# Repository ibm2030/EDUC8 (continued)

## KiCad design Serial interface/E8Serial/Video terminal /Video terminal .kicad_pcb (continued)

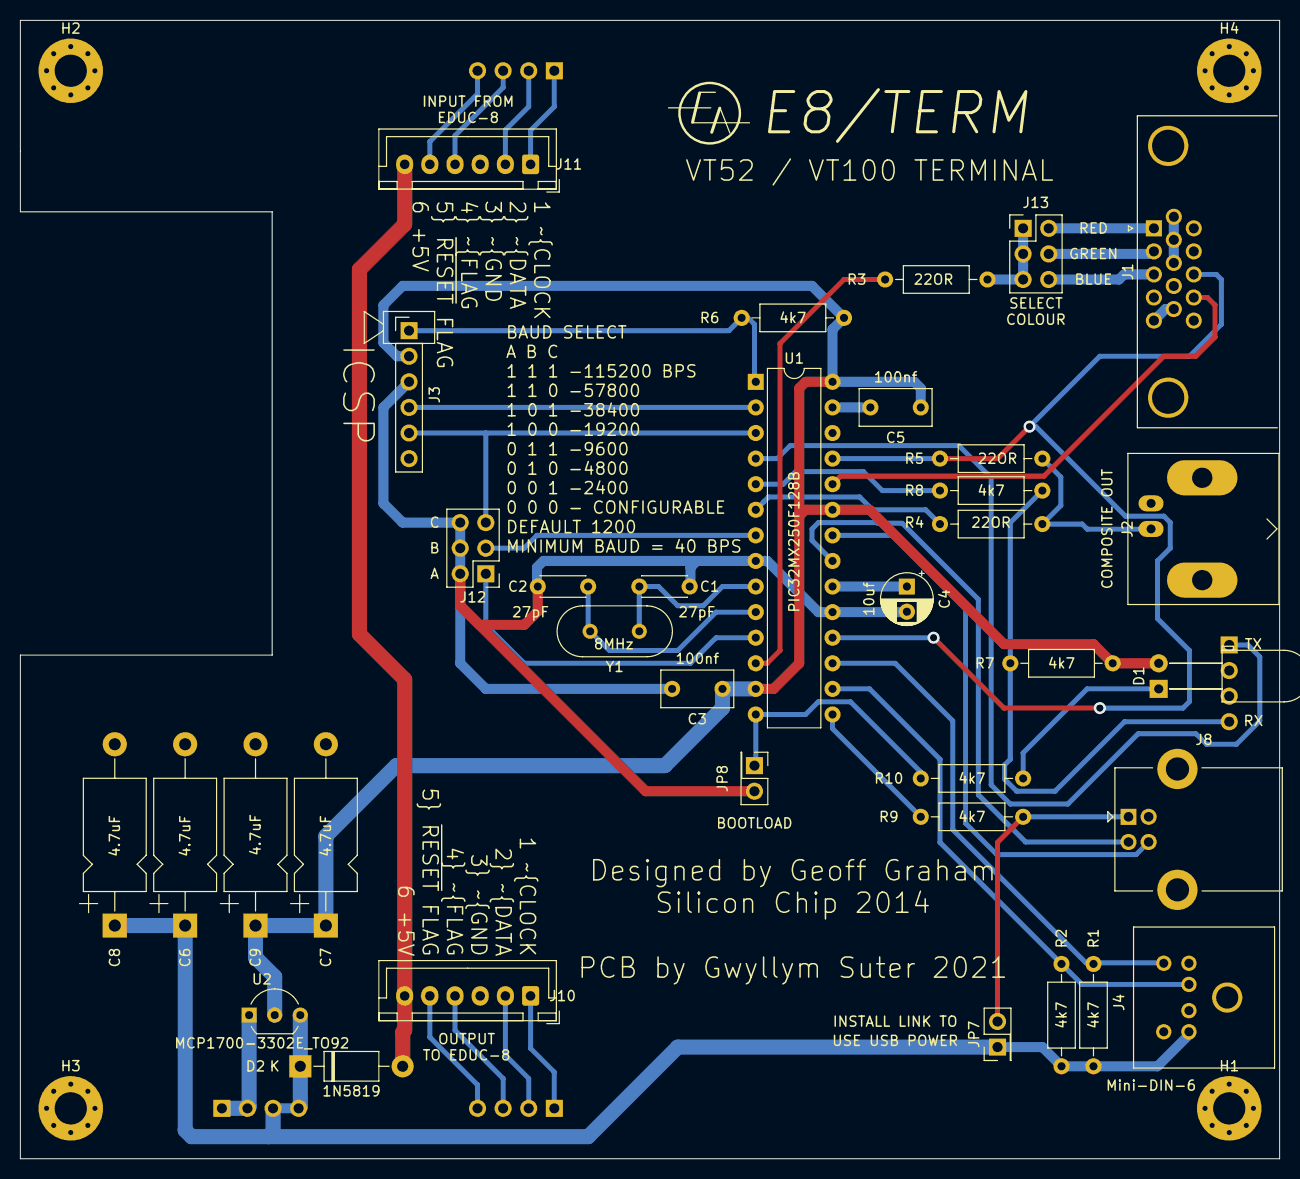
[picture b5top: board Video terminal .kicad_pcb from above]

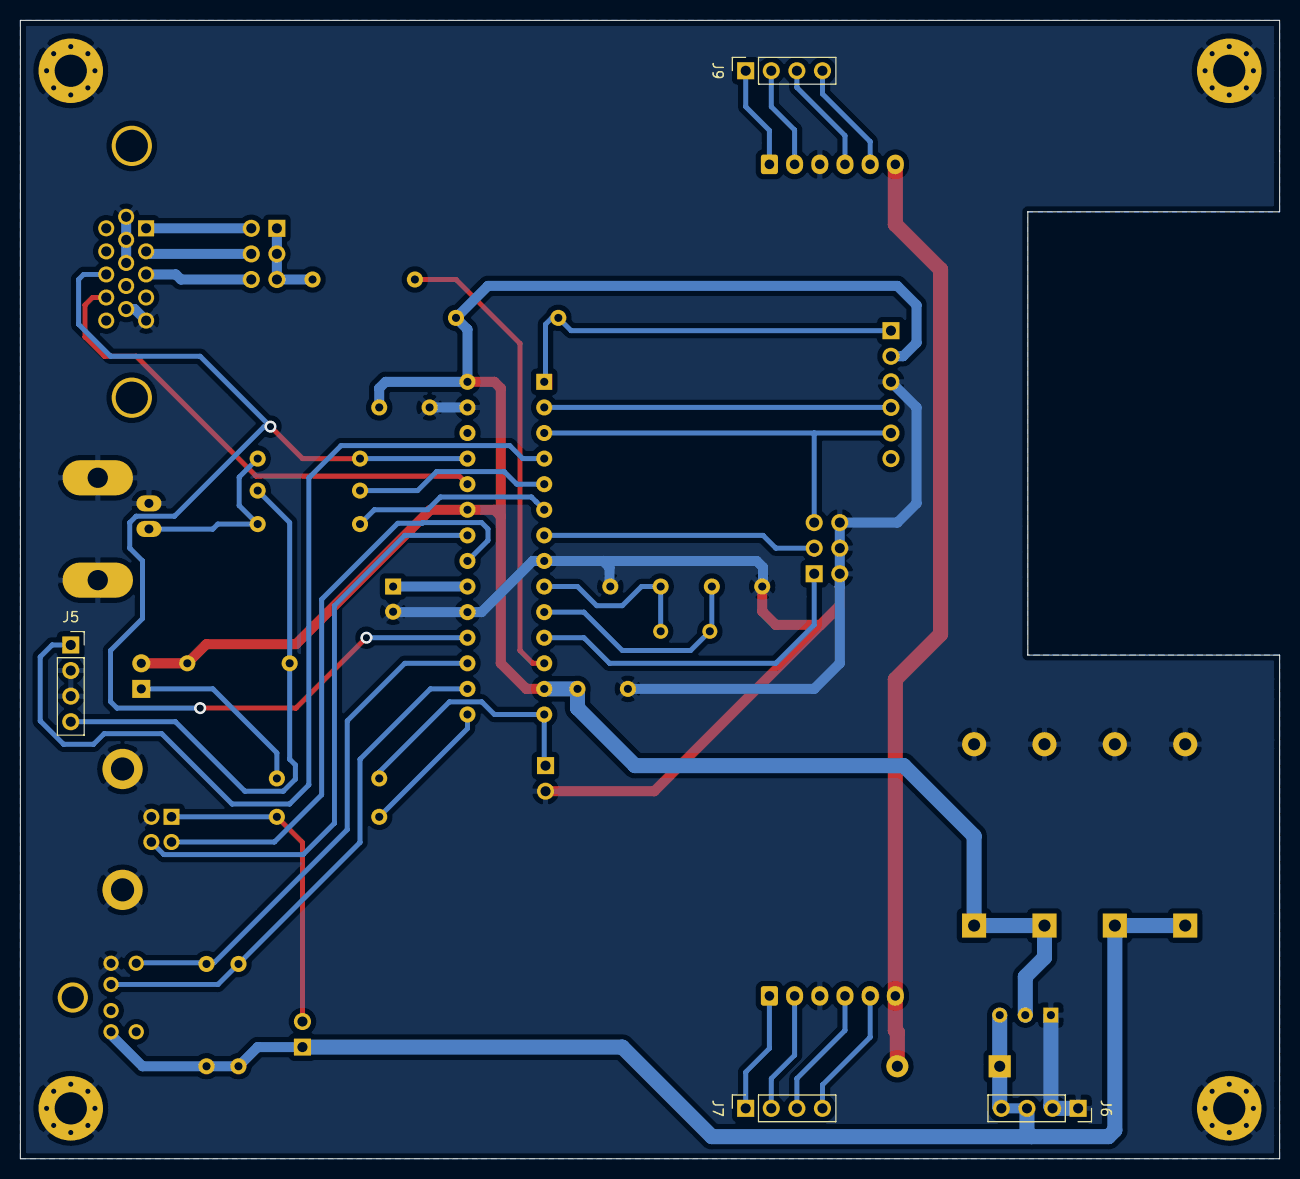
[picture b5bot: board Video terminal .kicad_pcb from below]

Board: 2 copper layers, 125.0 x 113.0 mm, 43 parts (4 on the bottom side), 40 nets.

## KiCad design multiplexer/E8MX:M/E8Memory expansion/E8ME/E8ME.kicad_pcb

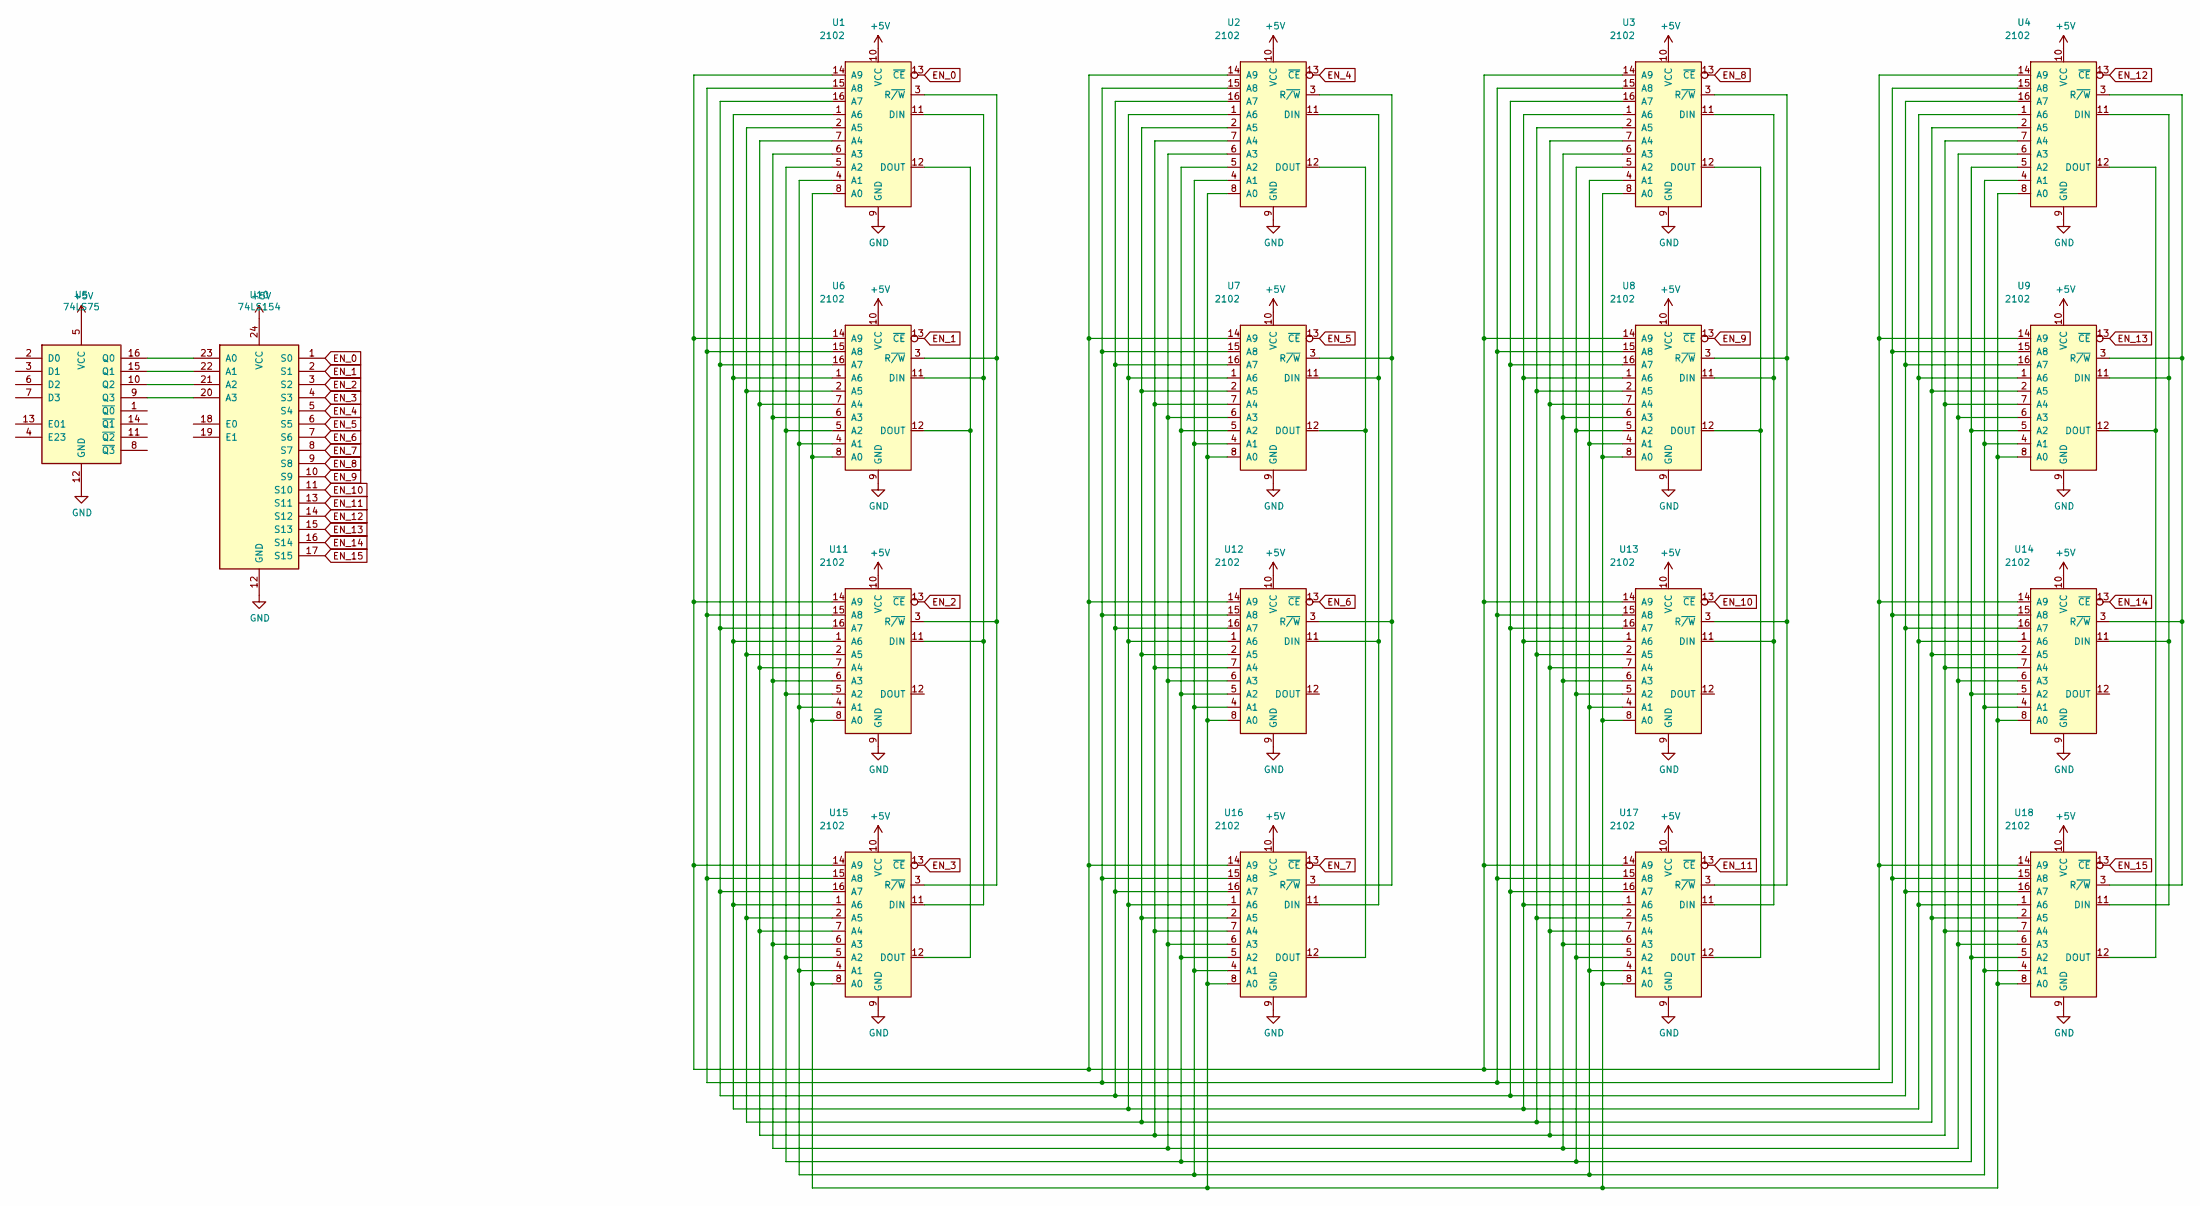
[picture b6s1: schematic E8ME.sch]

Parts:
U1, U2, U3, U4, U6, U7, U8, U9, U11, U12, U13, U14, U15, U16, U17, U18: 2102; DIP-16_W7.62mm_LongPads
U5: 74LS75; DIP-16_W7.62mm_LongPads
U10: 74LS154; DIP-24_W15.24mm_LongPads

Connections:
+5V: U1.10 (VCC), U2.10 (VCC), U3.10 (VCC), U4.10 (VCC), U5.5 (VCC), U6.10 (VCC), U7.10 (VCC), U8.10 (VCC), U9.10 (VCC), U10.24 (VCC), U11.10 (VCC), U12.10 (VCC), U13.10 (VCC), U14.10 (VCC), U15.10 (VCC), U16.10 (VCC), U17.10 (VCC), U18.10 (VCC)
EN_0: U1.13 (~CE), U10.1 (S0)
EN_1: U6.13 (~CE), U10.2 (S1)
EN_2: U10.3 (S2), U11.13 (~CE)
EN_3: U10.4 (S3), U15.13 (~CE)
EN_4: U2.13 (~CE), U10.5 (S4)
EN_5: U7.13 (~CE), U10.6 (S5)
EN_6: U10.7 (S6), U12.13 (~CE)
EN_7: U10.8 (S7), U16.13 (~CE)
EN_8: U3.13 (~CE), U10.9 (S8)
EN_9: U8.13 (~CE), U10.10 (S9)
EN_10: U10.11 (S10), U13.13 (~CE)
EN_11: U10.13 (S11), U17.13 (~CE)
EN_12: U4.13 (~CE), U10.14 (S12)
EN_13: U9.13 (~CE), U10.15 (S13)
EN_14: U10.16 (S14), U14.13 (~CE)
EN_15: U10.17 (S15), U18.13 (~CE)
GND: U1.9 (GND), U2.9 (GND), U3.9 (GND), U4.9 (GND), U5.12 (GND), U6.9 (GND), U7.9 (GND), U8.9 (GND), U9.9 (GND), U10.12 (GND), U11.9 (GND), U12.9 (GND), U13.9 (GND), U14.9 (GND), U15.9 (GND), U16.9 (GND), U17.9 (GND), U18.9 (GND)
unnamed: U1.1 (A6), U2.1 (A6), U3.1 (A6), U4.1 (A6), U6.1 (A6), U7.1 (A6), U8.1 (A6), U9.1 (A6), U11.1 (A6), U12.1 (A6), U13.1 (A6), U14.1 (A6), U15.1 (A6), U16.1 (A6), U17.1 (A6), U18.1 (A6)
unnamed: U1.2 (A5), U2.2 (A5), U3.2 (A5), U4.2 (A5), U6.2 (A5), U7.2 (A5), U8.2 (A5), U9.2 (A5), U11.2 (A5), U12.2 (A5), U13.2 (A5), U14.2 (A5), U15.2 (A5), U16.2 (A5), U17.2 (A5), U18.2 (A5)
unnamed: U1.3 (R~/W), U6.3 (R~/W), U11.3 (R~/W), U15.3 (R~/W)
unnamed: U1.4 (A1), U2.4 (A1), U3.4 (A1), U4.4 (A1), U6.4 (A1), U7.4 (A1), U8.4 (A1), U9.4 (A1), U11.4 (A1), U12.4 (A1), U13.4 (A1), U14.4 (A1), U15.4 (A1), U16.4 (A1), U17.4 (A1), U18.4 (A1)
unnamed: U1.5 (A2), U2.5 (A2), U3.5 (A2), U4.5 (A2), U6.5 (A2), U7.5 (A2), U8.5 (A2), U9.5 (A2), U11.5 (A2), U12.5 (A2), U13.5 (A2), U14.5 (A2), U15.5 (A2), U16.5 (A2), U17.5 (A2), U18.5 (A2)
unnamed: U1.6 (A3), U2.6 (A3), U3.6 (A3), U4.6 (A3), U6.6 (A3), U7.6 (A3), U8.6 (A3), U9.6 (A3), U11.6 (A3), U12.6 (A3), U13.6 (A3), U14.6 (A3), U15.6 (A3), U16.6 (A3), U17.6 (A3), U18.6 (A3)
unnamed: U1.7 (A4), U2.7 (A4), U3.7 (A4), U4.7 (A4), U6.7 (A4), U7.7 (A4), U8.7 (A4), U9.7 (A4), U11.7 (A4), U12.7 (A4), U13.7 (A4), U14.7 (A4), U15.7 (A4), U16.7 (A4), U17.7 (A4), U18.7 (A4)
unnamed: U1.8 (A0), U2.8 (A0), U3.8 (A0), U4.8 (A0), U6.8 (A0), U7.8 (A0), U8.8 (A0), U9.8 (A0), U11.8 (A0), U12.8 (A0), U13.8 (A0), U14.8 (A0), U15.8 (A0), U16.8 (A0), U17.8 (A0), U18.8 (A0)
unnamed: U1.11 (DIN), U6.11 (DIN), U11.11 (DIN), U15.11 (DIN)
unnamed: U1.12 (DOUT), U6.12 (DOUT), U15.12 (DOUT)
unnamed: U1.14 (A9), U2.14 (A9), U3.14 (A9), U4.14 (A9), U6.14 (A9), U7.14 (A9), U8.14 (A9), U9.14 (A9), U11.14 (A9), U12.14 (A9), U13.14 (A9), U14.14 (A9), U15.14 (A9), U16.14 (A9), U17.14 (A9), U18.14 (A9)
unnamed: U1.15 (A8), U2.15 (A8), U3.15 (A8), U4.15 (A8), U6.15 (A8), U7.15 (A8), U8.15 (A8), U9.15 (A8), U11.15 (A8), U12.15 (A8), U13.15 (A8), U14.15 (A8), U15.15 (A8), U16.15 (A8), U17.15 (A8), U18.15 (A8)
unnamed: U1.16 (A7), U2.16 (A7), U3.16 (A7), U4.16 (A7), U6.16 (A7), U7.16 (A7), U8.16 (A7), U9.16 (A7), U11.16 (A7), U12.16 (A7), U13.16 (A7), U14.16 (A7), U15.16 (A7), U16.16 (A7), U17.16 (A7), U18.16 (A7)
unnamed: U5.9 (Q3), U10.20 (A3)
unnamed: U5.10 (Q2), U10.21 (A2)
unnamed: U5.15 (Q1), U10.22 (A1)
unnamed: U5.16 (Q0), U10.23 (A0)
unnamed: U2.3 (R~/W), U7.3 (R~/W), U12.3 (R~/W), U16.3 (R~/W)
unnamed: U2.11 (DIN), U7.11 (DIN), U12.11 (DIN), U16.11 (DIN)
unnamed: U3.3 (R~/W), U8.3 (R~/W), U13.3 (R~/W), U17.3 (R~/W)
unnamed: U3.11 (DIN), U8.11 (DIN), U13.11 (DIN), U17.11 (DIN)
unnamed: U4.3 (R~/W), U9.3 (R~/W), U14.3 (R~/W), U18.3 (R~/W)
unnamed: U4.11 (DIN), U9.11 (DIN), U14.11 (DIN), U18.11 (DIN)
unnamed: U2.12 (DOUT), U7.12 (DOUT), U16.12 (DOUT)
unnamed: U3.12 (DOUT), U8.12 (DOUT), U17.12 (DOUT)
unnamed: U4.12 (DOUT), U9.12 (DOUT), U18.12 (DOUT)

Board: 2 copper layers, 18 parts (0 on the bottom side), 44 nets, no tracks yet.
